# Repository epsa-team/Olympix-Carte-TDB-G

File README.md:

Carte TDB gauche
================

Fournit un support mécanique au bargraphe indiquant le régime moteur

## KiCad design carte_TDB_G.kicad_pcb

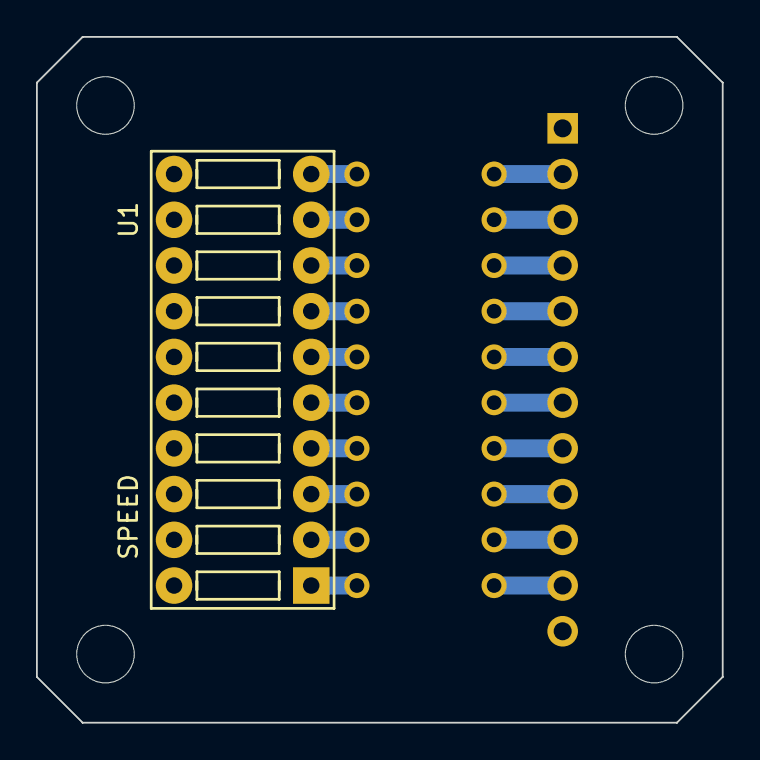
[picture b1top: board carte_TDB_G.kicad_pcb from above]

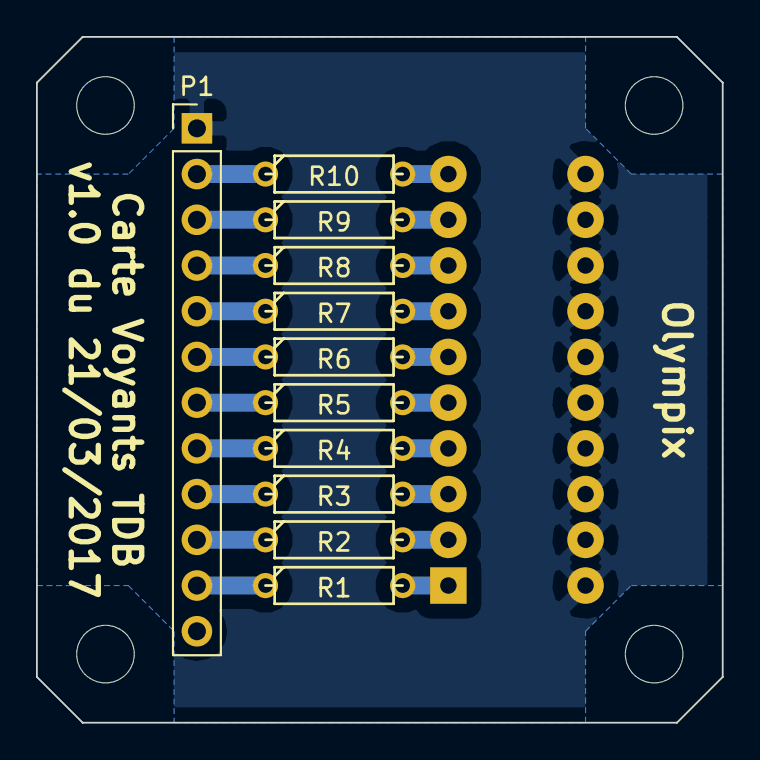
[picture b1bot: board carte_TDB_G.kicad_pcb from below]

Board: 2 copper layers, 38.1 x 38.1 mm, 12 parts (11 on the bottom side), 21 nets.

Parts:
P1: FROM_TDB; Pin_Header_Straight_1x12_Pitch2.54mm
R1, R2, R3, R4, R5, R6, R7, R8, R9, R10: 191; R3
U1: SPEED; HDSP-48xx

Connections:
GND: P1.1, U1.11, U1.12, U1.13, U1.14, U1.15, U1.16, U1.17, U1.18, U1.19, U1.20
unnamed: R1.2, U1.1
unnamed: R2.2, U1.2
unnamed: R3.2, U1.3
unnamed: R4.2, U1.4
unnamed: R5.2, U1.5
unnamed: R6.2, U1.6
unnamed: R7.2, U1.7
unnamed: R8.2, U1.8
unnamed: R9.2, U1.9
unnamed: R10.2, U1.10
bar_graph_1: P1.11, R1.1
bar_graph_2: P1.10, R2.1
bar_graph_3: P1.9, R3.1
bar_graph_4: P1.8, R4.1
bar_graph_5: P1.7, R5.1
bar_graph_6: P1.6, R6.1
bar_graph_7: P1.5, R7.1
bar_graph_8: P1.4, R8.1
bar_graph_9: P1.3, R9.1
bar_graph_10: P1.2, R10.1

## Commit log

2017-03-21 Validation du schématic
2017-03-21 Ajout du fichier .gitignore et suppression fichier .net
2017-03-21 Validation formelle
2017-03-21 Démonstration et validation routage
2017-03-21 Configuration paramètres de traçage GERBER
2017-03-21 Ajout du fichier README
